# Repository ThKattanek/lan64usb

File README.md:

# Lan64USB
Diese Hard- und Software ermöglicht den Transfer von Programmen vom PC zum Commodore 64 (C64).

### Hardware / Schaltplan / Treiber
Die Hardware wurde mit KiCad entwickelt. Version 4.0.7 unter Ubuntu.

Mit diesem Tool wird das Treiber Setup Programm erstellt. (LibUSB-Win32)

https://sourceforge.net/projects/libusb-win32/files/libusbK-release/

### Anleitung ist hier nur für Linux User !

## Vorraussetzungen

Wird noch ergänzt !!

## Komplettes Repositorie auf dem PC laden
```bash
cd ~
git clone https://github.com/ThKattanek/lan64usb.git
```

## Erstellen der PC Anwendung "Lan64Tool"
```bash
cd ~/lan64usb/pc-software/lan64tool
mkdir build
cd build
qmake ..
make
```
## Erstellen des Konsolentools lan64-send"
```bash
cd ~/lan64usb/pc-software/konsolen_tools/lan64_send
mkdir build
cd build
qmake ..
make
```

## AVR Firmware erstellen und flashen
```bash
cd ~/lan64usb/firmware
make hex        // Erstellt das Binary
make program    // Flasht das Binary auf den avr mit avrdude (evtl. anpassen an eueren Programmer)
make clean      // Alles wieder aufräumen
```

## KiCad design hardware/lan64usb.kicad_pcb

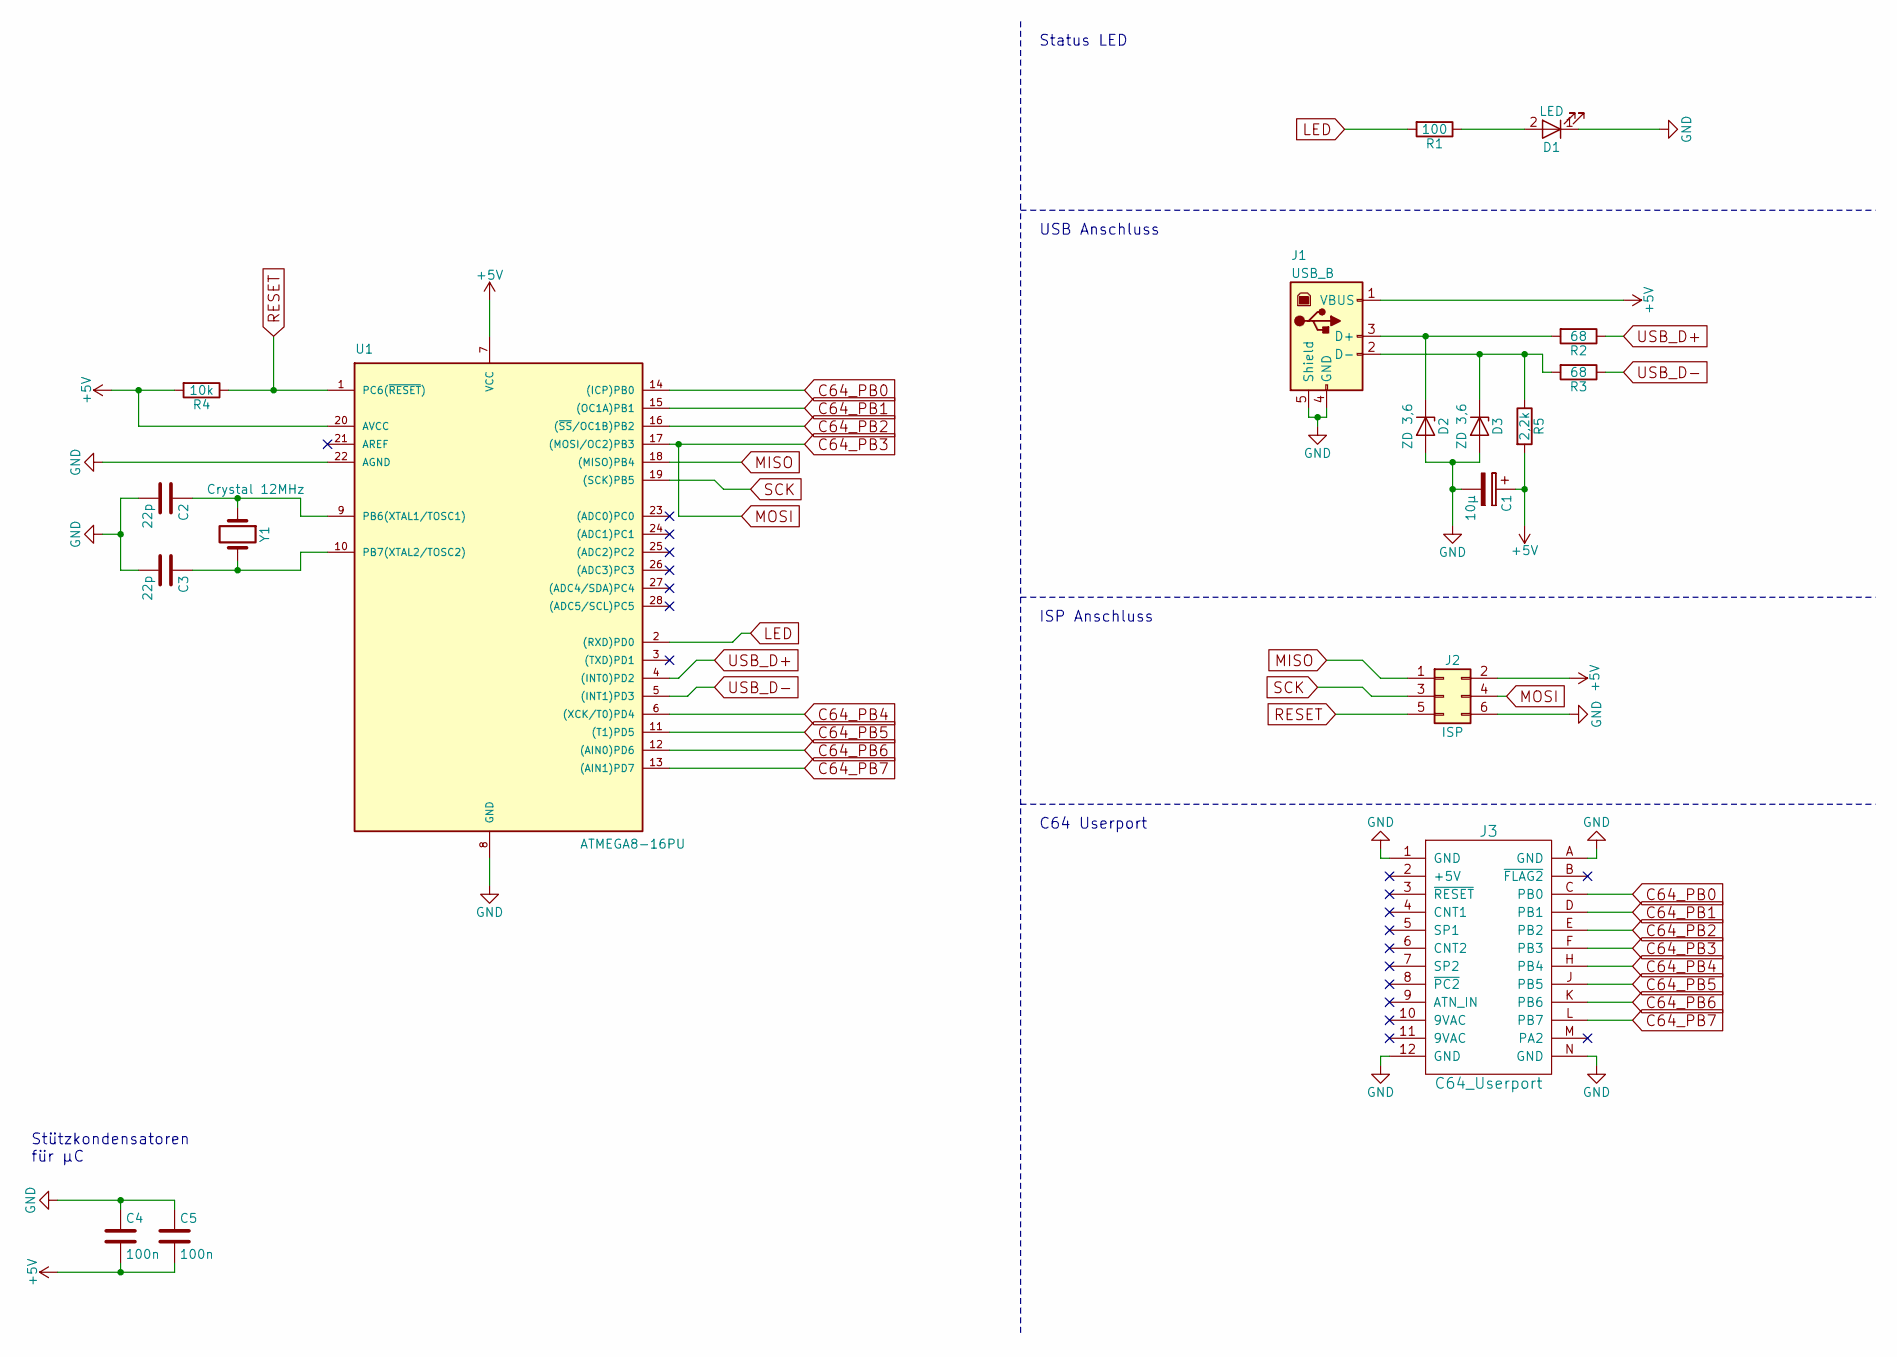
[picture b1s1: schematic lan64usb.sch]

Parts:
C1: 10µ; CP_5x11mm
C2, C3: 22p; C_Disc_D4.7mm_W2.5mm_P5.00mm
C4, C5: 100n; C_Disc_D3.8mm_W2.6mm_P2.50mm
D1: LED; led_3mm_green
D2, D3: ZD 3,6; D_DO-35_SOD27_P7.62mm_Horizontal
J1: USB_B
J2: ISP; vasch_strip_3x2
J3: C64_Userport; c64_userport
R1: 100; R_Axial_DIN0207_L6.3mm_D2.5mm_P10.16mm_Horizontal
R2, R3: 68; R_Axial_DIN0207_L6.3mm_D2.5mm_P10.16mm_Horizontal
R4: 10k; R_Axial_DIN0207_L6.3mm_D2.5mm_P10.16mm_Horizontal
R5: 2,2k; R_Axial_DIN0207_L6.3mm_D2.5mm_P10.16mm_Horizontal
U1: ATMEGA8-16PU; dil_28-300_socket
Y1: Crystal 12MHz; Crystal_HC49-4H_Vertical

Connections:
+5V: C1.1, C4.2, C5.2, J1.1 (VBUS), J2.2, R4.2, R5.2, U1.7 (VCC), U1.20 (AVCC)
C64_PB0: J3.C (PB0), U1.14 ((ICP)PB0)
C64_PB1: J3.D (PB1), U1.15 ((OC1A)PB1)
C64_PB2: J3.E (PB2), U1.16 ((~SS~/OC1B)PB2)
C64_PB3: J2.4, J3.F (PB3), U1.17 ((MOSI/OC2)PB3)
C64_PB4: J3.H (PB4), U1.6 ((XCK/T0)PD4)
C64_PB5: J3.J (PB5), U1.11 ((T1)PD5)
C64_PB6: J3.K (PB6), U1.12 ((AIN0)PD6)
C64_PB7: J3.L (PB7), U1.13 ((AIN1)PD7)
GND: C1.2, C2.2, C3.2, C4.1, C5.1, D1.1 (K), D2.2 (A), D3.2 (A), J1.4 (GND), J1.5 (Shield), J2.6, J3.1 (GND), J3.12 (GND), J3.A (GND), J3.N (GND), U1.8 (GND), U1.22 (AGND)
LED: R1.2, U1.2 ((RXD)PD0)
MISO: J2.1, U1.18 ((MISO)PB4)
unnamed: C2.1, U1.9 (PB6(XTAL1/TOSC1)), Y1.1
unnamed: C3.1, U1.10 (PB7(XTAL2/TOSC2)), Y1.2
unnamed: D1.2 (A), R1.1
unnamed: D2.1 (K), J1.3 (D+), R2.2
unnamed: D3.1 (K), J1.2 (D-), R3.2, R5.1
RESET: J2.5, R4.1, U1.1 (PC6(~RESET~))
SCK: J2.3, U1.19 ((SCK)PB5)
USB_D+: R2.1, U1.4 ((INT0)PD2)
USB_D-: R3.1, U1.5 ((INT1)PD3)

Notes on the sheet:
Stützkondensatoren für µC
Status LED
USB Anschluss
ISP Anschluss
C64 Userport

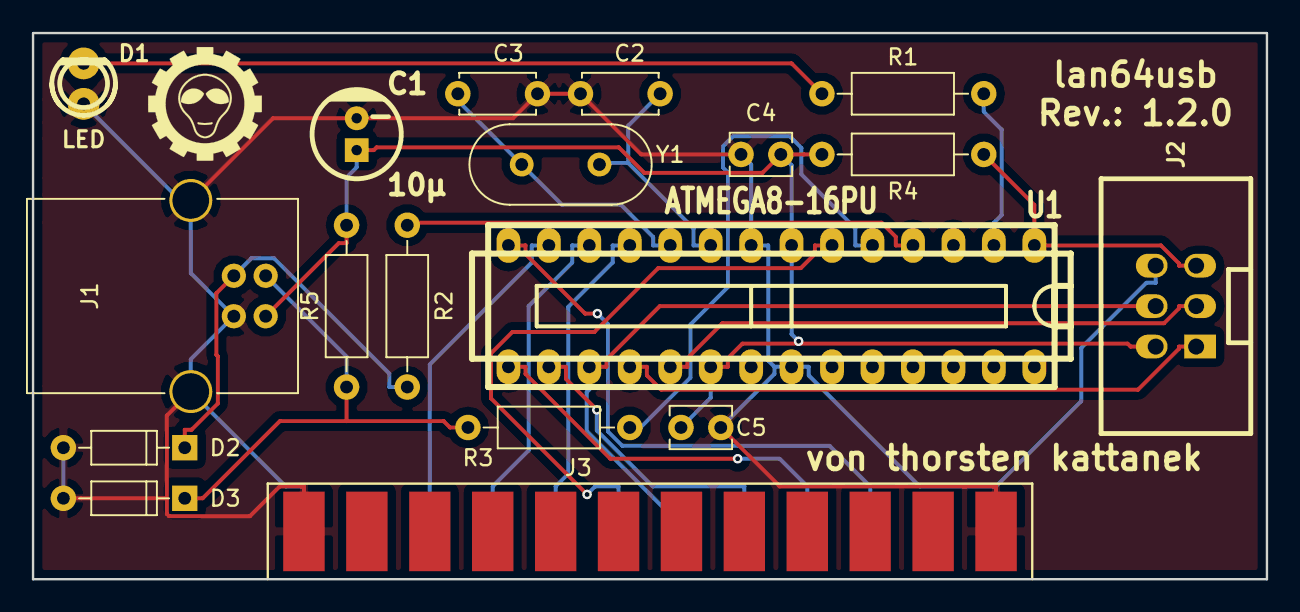
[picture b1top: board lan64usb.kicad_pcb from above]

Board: 2 copper layers, 77.5 x 34.3 mm, 18 parts (0 on the bottom side), 21 nets.

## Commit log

2014-05-10 Start des Projektes
2014-05-10 Projekt Datei angepasst
2014-05-10 Schaltplan Version 1.00 hinzugefuegt
2014-05-10 C64 Software hinzugefuegt
2014-05-11 Verbindung mit Lan64USB
2014-05-11 Noch keine Uebertragung moeglich
2014-05-12 128 Byte Puffer Variante Funktioniert nun
2014-05-12 PRG Transfer hinzugefuegt
2014-05-13 - Nach Fehlgeschlagener Uerbertragung musste der Adapter getrennt werden. Dies ist nicht mehr noetig
2014-05-18 *.c64 Datei mit hinzugefuegt
2014-05-18 nach utf-8 konvertiert
2014-05-21 Fix - Dateifilter bei Dateisystem ging nicht
2015-01-09 - Projekt neu geordnet
2015-01-09 - konsolen_tools gelöscht
2015-01-09 - lan64_send hinzugefuegt
2015-01-09 - gerade gezogen
2015-01-09 - deployment.pri entfernt
2015-01-09 lan64tool.cpp --> lan64usb_class.cpp lan64tool.h --> lan64usb_class.h
2015-01-09 lan64_send funktioniert erstmal
2015-01-25 Schaltplan überarbeitet auf Version 1.0.1
2017-11-08 qt projektdatei angepasst für installer
2017-11-08 -gitignore hinzugefügt
2017-11-08 Doppeltes Unterverzeichnis entfernt
2018-04-15 trutf8 bei den Texten der Message Ausgaben hinzugefügt. Somit wird bei immer die richtige Codierung des Textes für das jeweilige System eingesetzt.
2018-05-15 repository struktur geändert
2018-05-15 .gitignore geändert
2018-05-15 LICESE hinzugefügt
2018-05-15 usbdrv zur firmware hinzugefügt
2018-05-15 lan64usb_class.h an neue Datei Struktur angepasst
2018-05-15 readme.md hinzugefügt.
2018-05-15 README.md angepasst.
2018-05-15 Angefangen den Schaltplan in KiCAD zu zeichnen.
2018-05-16 Schaltplan in KiCad fertig gezeichnet. Rev auf 1.1.0 gesetzt.
2018-05-17 Schaltplan für DIP Bauteile angepasst. Rev.: 1.2.0
2018-05-17 Alle Footprints zugeordnet und Net Liste erstellt.
2018-05-17 Ein erstes PCB Layout erstellt.
2018-05-17 3D Ansicht hinzugefügt. Stecker fehlt noch!
2018-05-20 3D Modell des Userport Steckers eingefügt.
2018-05-26 lan64tool: Projekt nach CMake portiert.
2018-05-26 .gitignore angepasst
2018-05-26 lan64tool: hiddata.h / hiddata.c entfernt
2018-05-26 lan64tool: CMakeLists.txt angepasst für Windows Crosscompiling.
2018-05-26 firmware: Vendor Name auf https://github/ThKattanek geändert.
2018-05-26 firmware: Divename geändert -> lan64usb
2018-05-27 lan64tool: open(), openDevice() und closeDevice() fertig umgestellt auf libusb-1.0
2018-05-27 lan64tool: komplette Umstellung auf libusb-1.0
